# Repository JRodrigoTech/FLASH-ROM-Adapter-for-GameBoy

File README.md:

# SOP-32L FLASH to ROM Adapter for Game Boy Cartridges

---

# TSOP-44L FLASH to ROM Adapter

#### NOTE : This adaptar this pretty hard to solder. If you are new in soldering, I recommend to use the SOP32 adapter because is much more easy to solder and fix.

---

## Compatible Flashes

AM29F016@-#E* (2 MB) or AM29F032@-#E* (4 MB)
```
 @ = Manufactured process technology (None = 0.5 µm, B = 0.32 µm, D = 0.23 µm)
 # = any speeds are compatible (75,90,120,150)
 E = 48-Pin Thin Small Outline Package (TSOP) Standard Pinout (TS 048)
 * = any temperature range (C = Commercial (0°C to +70°C) or I = Industrial (-40°C to +85°C))
```
*Ex: AM29F016-75EC, AM29F032B-120EI,...* 

---

## [How To - Assembly Guide](http://www.jrodrigo.net/wiki/how-to-diy-a-gameboy-flash-cartridge-with-a-rom-adapter-board/)

## Where to buy :package:
- [**Tindie** with optional presolded 2MB/4MB ROM](https://www.tindie.com/products/JRodrigo/flash-memory-adapter-for-some-game-boy-cartridges/)
- [**OSHpark** (SOP32 bare PCBs only)](https://oshpark.com/shared_projects/5S5OQRXm)
- [**OSHpark** (TSOP44 bare PCBs only)](https://oshpark.com/shared_projects/Ks4WbXlo)
- [**PCBWay** (SOP32 bare PCBs only)](https://www.pcbway.com/project/shareproject/Flash_Memory_Adapter_for_Game_Boy.html)

---

## License
#### Licenced under [Creative Commons - Attribution and Share Alike](https://github.com/JRodrigoTech/FLASH-ROM-Adapter-for-GameBoy/blob/master/LICENSE.md) by [J.Rodrigo](http://www.jrodrigo.net)

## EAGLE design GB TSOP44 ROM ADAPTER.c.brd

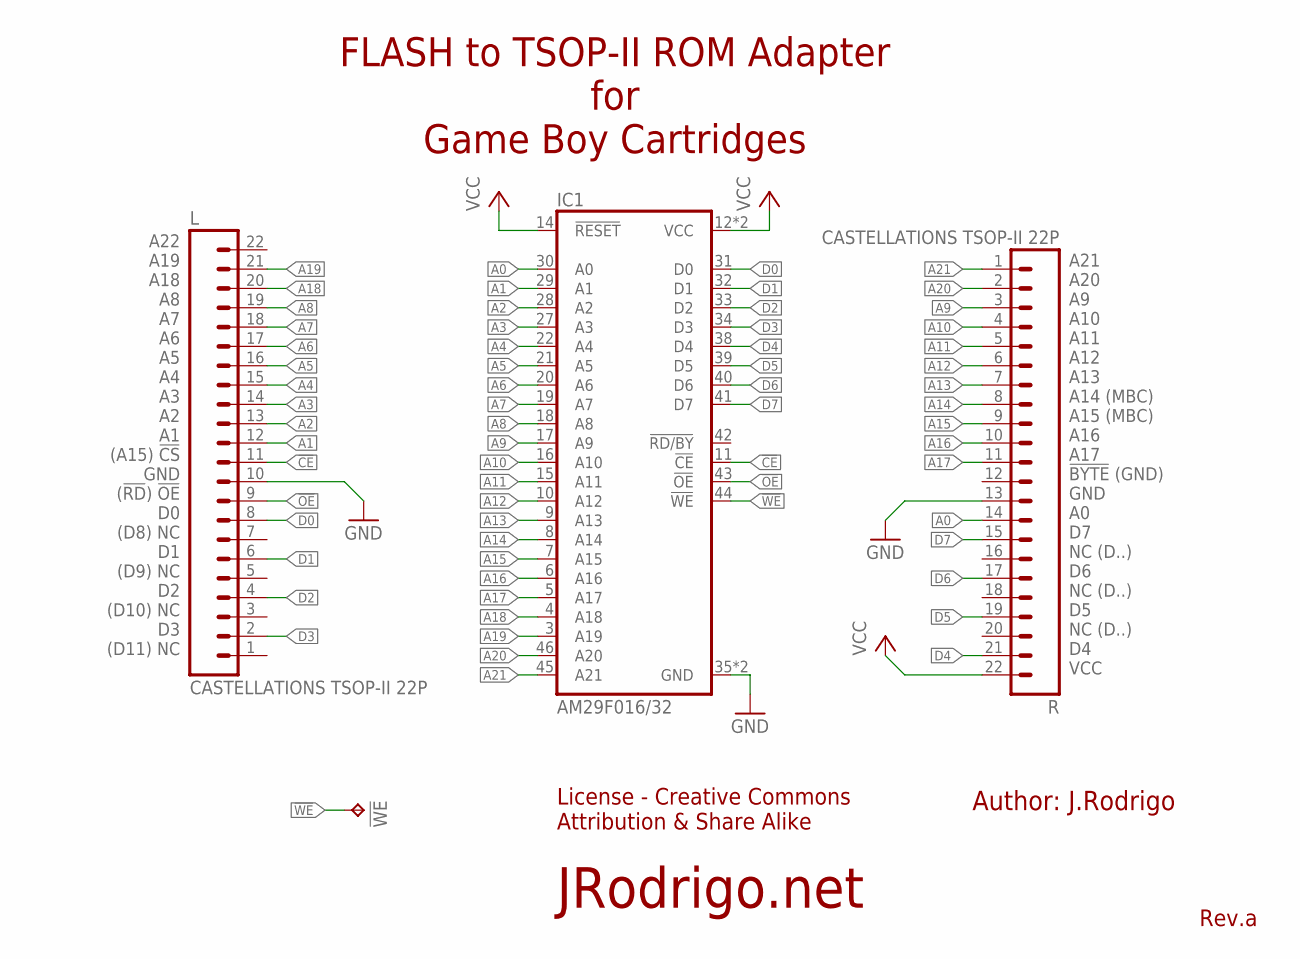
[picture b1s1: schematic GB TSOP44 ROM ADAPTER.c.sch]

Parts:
!WE: TPTP06SQ; TP06SQ
IC1: AM29F016/32; TSOP48-2
L: CASTELLATIONS TSOP-II 22P; CASTELLATIONS_TSOP_II_22PHH
R: CASTELLATIONS TSOP-II 22P; CASTELLATIONS_TSOP_II_22PHH

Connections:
!CE: IC1.11 (!CE), L.11
!OE: IC1.43 (!OE), L.9
!WE: !WE.TP, IC1.44 (!WE)
A0: IC1.30 (A0), R.14
A1: IC1.29 (A1), L.12
A2: IC1.28 (A2), L.13
A3: IC1.27 (A3), L.14
A4: IC1.22 (A4), L.15
A5: IC1.21 (A5), L.16
A6: IC1.20 (A6), L.17
A7: IC1.19 (A7), L.18
A8: IC1.18 (A8), L.19
A9: IC1.17 (A9), R.3
A10: IC1.16 (A10), R.4
A11: IC1.15 (A11), R.5
A12: IC1.10 (A12), R.6
A13: IC1.9 (A13), R.7
A14: IC1.8 (A14), R.8
A15: IC1.7 (A15), R.9
A16: IC1.6 (A16), R.10
A17: IC1.5 (A17), R.11
A18: IC1.4 (A18), L.20
A19: IC1.3 (A19), L.21
A20: IC1.46 (A20), R.2
A21: IC1.45 (A21), R.1
D0: IC1.31 (D0), L.8
D1: IC1.32 (D1), L.6
D2: IC1.33 (D2), L.4
D3: IC1.34 (D3), L.2
D4: IC1.38 (D4), R.21
D5: IC1.39 (D5), R.19
D6: IC1.40 (D6), R.17
D7: IC1.41 (D7), R.15
GND: IC1.35 (GND), IC1.36 (GND), L.10, R.13
VCC: IC1.12 (VCC), IC1.14 (!RESET), IC1.37 (VCC), R.22

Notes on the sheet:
FLASH to TSOP-II ROM Adapter for Game Boy Cartridges
Rev.a
Author: J.Rodrigo
License - Creative Commons Attribution & Share Alike
JRodrigo.net
A22 A19 A18 A8 A7 A6 A5 A4 A3 A2 A1 (A15) !CS! GND (!RD!) !OE! D0 (D8) NC D1 (D9) NC D2 (D10) NC D3 (D11) NC
A21 A20 A9 A10 A11 A12 A13 A14 (MBC) A15 (MBC) A16 A17 !BYTE! (GND) GND A0 D7 NC (D..) D6 NC (D..) D5 NC (D..) D4 VCC

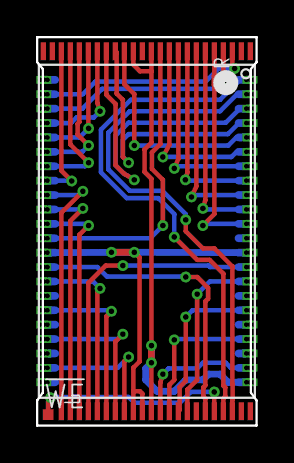
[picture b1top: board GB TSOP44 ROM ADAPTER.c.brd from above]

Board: 2 copper layers, 12.2 x 21.6 mm, 4 parts (0 on the bottom side), 35 nets.

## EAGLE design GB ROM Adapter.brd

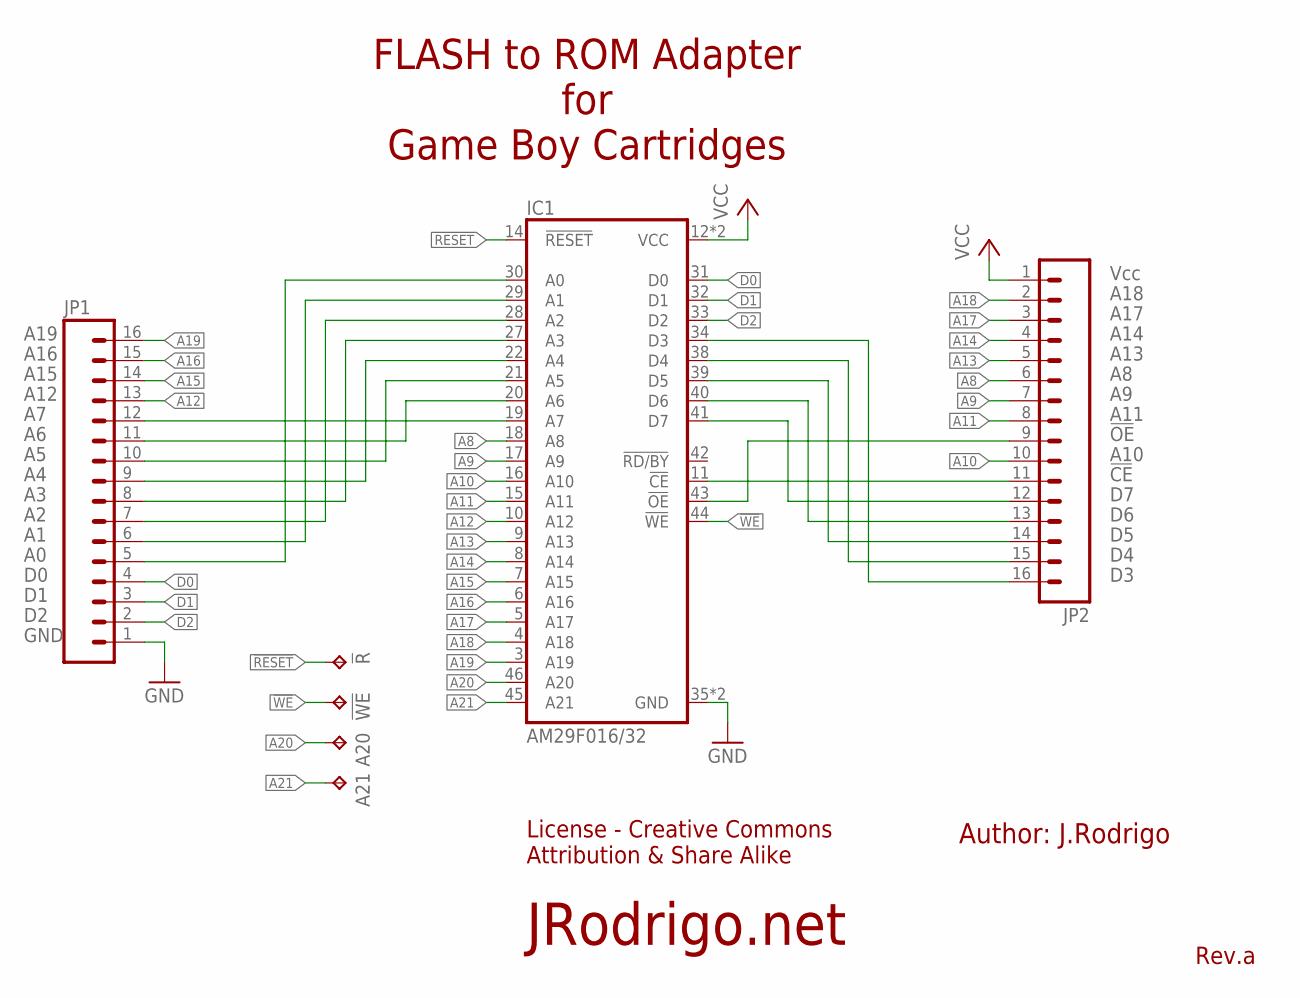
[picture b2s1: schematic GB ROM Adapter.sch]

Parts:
!R: TPTP08SQ; TP08SQ
!WE: TPTP08SQ; TP08SQ
A20, A21: TPTP08SQ; TP08SQ
IC1: AM29F016/32; TSOP48
JP1, JP2: CASTELLATIONS_16-PINS*; CASTELLATIONS_16-PINS

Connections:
!RESET: !R.TP, IC1.14 (!RESET)
!WE: !WE.TP, IC1.44 (!WE)
A8: IC1.18 (A8), JP2.6
A9: IC1.17 (A9), JP2.7
A10: IC1.16 (A10), JP2.10
A11: IC1.15 (A11), JP2.8
A12: IC1.10 (A12), JP1.13
A13: IC1.9 (A13), JP2.5
A14: IC1.8 (A14), JP2.4
A15: IC1.7 (A15), JP1.14
A16: IC1.6 (A16), JP1.15
A17: IC1.5 (A17), JP2.3
A18: IC1.4 (A18), JP2.2
A19: IC1.3 (A19), JP1.16
A20: A20.TP, IC1.46 (A20)
A21: A21.TP, IC1.45 (A21)
D0: IC1.31 (D0), JP1.4
D1: IC1.32 (D1), JP1.3
D2: IC1.33 (D2), JP1.2
GND: IC1.35 (GND), IC1.36 (GND), JP1.1
unnamed: IC1.34 (D3), JP2.16
unnamed: IC1.38 (D4), JP2.15
unnamed: IC1.39 (D5), JP2.14
unnamed: IC1.40 (D6), JP2.13
unnamed: IC1.41 (D7), JP2.12
unnamed: IC1.11 (!CE), JP2.11
unnamed: IC1.43 (!OE), JP2.9
unnamed: IC1.29 (A1), JP1.6
unnamed: IC1.28 (A2), JP1.7
unnamed: IC1.30 (A0), JP1.5
unnamed: IC1.27 (A3), JP1.8
unnamed: IC1.22 (A4), JP1.9
unnamed: IC1.21 (A5), JP1.10
unnamed: IC1.20 (A6), JP1.11
unnamed: IC1.19 (A7), JP1.12
VCC: IC1.12 (VCC), IC1.37 (VCC), JP2.1

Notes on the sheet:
A19
A16
A15
A12
GND
Vcc
A18
A17
A14
A13
A11
!OE
A10
!CE
FLASH to ROM Adapter for Game Boy Cartridges
Rev.a
Author: J.Rodrigo
License - Creative Commons Attribution & Share Alike
JRodrigo.net

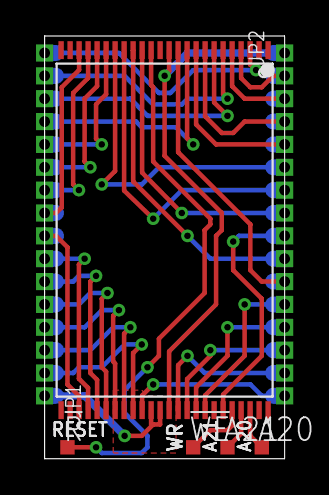
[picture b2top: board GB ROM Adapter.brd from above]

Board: 2 copper layers, 13.3 x 23.5 mm, 7 parts (0 on the bottom side), 36 nets.

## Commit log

2017-01-28 Initial commit of LICENSE.md
2017-01-28 Initial commit of README.md
2017-01-28 Initial board release
    Some boards ordered to OSHpark, untested onboard.
2017-02-20 Update of README.md
    Board are tested and fully working, coming soon on Tindie.
2017-03-28 Updated silk screen
2017-04-07 Update README.md
    Added the assembly guide and "where to buy", removed the "ToDo" section.
2017-11-03 Updated buy links on README.md
2018-12-25 First files version renamed to SOP44
2018-12-25 New TSOP44 adapter files
2018-12-25 First files version fixed renamed to SOP32 ✌️
2018-12-25 Updated Readme
    - Added TSOP44 adapter preview image
    - Added TSOP44 OSHPark buy link
2019-08-08 Created FUNDING.yml file
